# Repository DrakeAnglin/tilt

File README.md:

# Tilt

Most smart blinds need one device per blind. Tilt uses **one controller for up to three blinds**, and each blind
still has its own name in Apple Home and Alexa, its own Schedule and its own tilt.

- **One blind:** 1 tilter + 1 controller + 1 Tilt Hub.
- **Up to three blinds:** more tilters on the same controller.
- **More blinds:** another controller for each three. Still one Tilt Hub for the whole home.

Tilt is open-source, 3D-printable motorized **tilt** for cordless horizontal blinds. Each blind gets a printed tilter
in its headrail; the wand still works by hand. A battery-powered controller drives up to 3 blinds. Control is from the
**Tilt** iPhone app, **Apple Home** and **Alexa**, through a **Tilt Hub**: the controllers talk Thread to the hub and
sleep, and the hub is the Matter device for every blind. No cloud, no account.

Only the current version of each thing is kept here. Older versions are in the Git history.

## Start here
- **Build one:** [docs/build-guide.md](docs/build-guide.md): one blind start to finish, then more blinds.
- **What to buy:** [hardware/BOM.md](hardware/BOM.md), with how many of each for your number of blinds.
- **How it works:** [docs/architecture.md](docs/architecture.md). Words used everywhere: [CONTEXT.md](CONTEXT.md).
- **What to do next:** [GitHub issues](https://github.com/DrakeAnglin/tilt/issues). There are no to-do files.

## Build one
| Page | What |
|---|---|
| [build-guide.md](docs/build-guide.md) | The whole build, in order |
| [hardware/BOM.md](hardware/BOM.md) | Parts to buy, and how many |
| [measure-your-blinds.md](docs/measure-your-blinds.md) | Measuring blinds that differ from the reference blinds |
| [Tilter](hardware/mechanical/stl/tilter/README.md), [sensor module](docs/tilter-wiring.md), [mechanical build](docs/tilter-assembly.md) | Printing, wiring and assembling a tilter |
| [pcb-build.md](docs/pcb-build.md), [controller-box.md](docs/controller-box.md) | Soldering the controller PCB; the box |
| [hub-box.md](docs/hub-box.md) | The Tilt Hub's box |
| [firmware/README.md](firmware/README.md), [Tilt Hub](firmware/tilt_hub/README.md) | Flashing and updates |

## Work on Tilt
For people working on Tilt itself. You do not need any of this to build one.

| Page | What |
|---|---|
| [architecture.md](docs/architecture.md), [requirements.md](docs/requirements.md) | How it works; what it must do |
| [CONTEXT.md](CONTEXT.md) | The words used everywhere |
| [docs/adr](docs/adr) | Decisions on record |
| [docs/developer](docs/developer/README.md) | App Store notes, firmware releases, security hardening, the agent workflow |
| [pcb-v3-concept.md](docs/pcb-v3-concept.md) | The next PCB (design proposal) |

### What is in here
| Folder | What |
|---|---|
| [app/Tilt](app/README.md) | The iPhone app (SwiftUI) with its widget and Control Center buttons |
| [firmware/blinds_matter](firmware/README.md) | Controller firmware (ESP32-C6, ESP-IDF + esp-matter) |
| [firmware/tilt_hub](firmware/tilt_hub/README.md) | Tilt Hub firmware |
| [firmware/as5600_setup](firmware/README.md#as5600_setup-sensor-bench-tool) | Bench tool that switches a new AS5600 angle sensor to PWM output |
| [hardware/mechanical](hardware/mechanical/README.md) | Tilter and controller box: Fusion 360 generators and print files; headrail measurements |
| [hardware/pcb](hardware/pcb/README.md) | Controller PCB v2.2 |
| [tools](tools) | Build, check and print helpers (below) |
| [docs](docs) | Guides, notes, reference photos (`docs/reference/`) |

### Tools
| Tool | Does |
|---|---|
| `tools/fusion_tilter.py` | Builds the tilter in Fusion, runs the collision and gear checks, exports STLs |
| `tools/fusion_thin.py` | Thin-wall scan of the built tilter |
| `tools/orient.py`, `tools/bambu.py` | Turn the STLs to print orientation; build the Bambu Studio projects (PLA plate + PETG plate) |
| `tools/fusion_controller.py` | Builds the controller box in Fusion |
| `tools/flash.sh` | Builds the controller firmware and installs it through the Tilt Hub |
| `tools/flash_hub.sh` | Builds the Tilt Hub firmware and installs it over Wi-Fi; `--usb <port>` for its first flash |
| `tools/device_identity.py` | A first USB flash (`flash_hub.sh --usb`, `flash.sh --usb`): a hub's Apple Home code and setup code, made on the Mac, saved in `~/.tilt/devices/`, and its setup label (`labels` prints one again) |
| `tools/release_firmware.py` | Builds and signs a public firmware release (a version tag runs it in GitHub Actions: `docs/developer/firmware-release.md`) |
| `tools/blinds_client.py` | Talks to a controller over its secured channel (testing) |
| `tools/pcb_guide.py` | Generates the PCB build guide and its pictures |
| `tools/check_docs.py` | Checks the docs: links, anchors, and no leftovers from one house |
| `tools/firmware_tests.sh`, `tools/app_tests.sh`, `tools/test_tools.py` | Tests |
| `tools/host_cjson.py` | Finds the real cJSON (ESP-IDF's copy, else the system's) for the Tilt Hub's Mac tests |
| `tools/coverage.sh`, `tools/coverage_gate.py` | Line coverage of the tests, and the gate every pull request must pass (below) |

Fusion scripts run through the FusionBridge add-in: `python3 hardware/mechanical/fusion/fusion.py exec tools/<script>.py`.

### Coverage
<!-- coverage:start -->

| Area | Line coverage |
|---|---|
| Tilt app | at least 23% |
| controller firmware | at least 76% |
| Tilt Hub firmware | at least 17% |
| tools | at least 99% |

Every pull request covers at least 90% of the lines it changes in our own code, and no area may drop under its floor (`tools/coverage-floors.txt`). The live numbers: the `coverage` job of the [latest CI run on main](https://github.com/DrakeAnglin/tilt/actions/workflows/ci.yml?query=branch%3Amain). The rule: [docs/agents/workflow.md](docs/agents/workflow.md#coverage).
<!-- coverage:end -->

## License
- Code (firmware, app, tools, docs): [MIT](LICENSE).
- Hardware (`hardware/`: CAD, printed parts, PCB, BOM): [CC BY-NC-SA 4.0](hardware/LICENSE.md). Build it and share it, but do not sell it.

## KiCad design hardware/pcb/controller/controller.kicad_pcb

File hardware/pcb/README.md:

# Controller PCB (v2.2, carrier board)

**v2.2 (2026-11-07): the jack edge is 3.5 mm shorter.** For the controller box's end wall, the RJ12 jacks come through
the wall, so the board's jack edge moves 3.5 mm in and the jacks overhang it by 2.95 mm. Everything else is v2.1:
same parts, same copper, same holes. Only the outline moved, the ground fill pulled back with it, and the 11 ground
stitching vias that sat 2 mm from the old edge are gone. Back silkscreen reads "v2.2". The v2.1 boards already
made get the same edge cut by hand, 3–4 mm (see [the build guide, step 0](../../docs/pcb-build.md)). v2.1 as ordered
is tagged `pcb-v2.1-ordered` in git.

The controller's board: a 2-layer PCB where the **ESP32-C6 SuperMini** plugs into female header sockets; the
**18650**, the **charger** (an **Adafruit 6092**, through a 6-pin harness) and the optional **solar panel** plug into
three *different* JST headers; the **three RJ12 jacks** sit on the board edge with a fuse and
protection resistors behind each. Everything is through-hole and hand-soldered; there is no hand wiring.

The board was drawn for an MCP73871 charger module and a separate USB-C board (J3). The build now uses the Adafruit
6092 with its own USB-C instead, with no copper change: the harness and the battery splice in the J5 plug are in
[the build guide, step 11](../../docs/pcb-build.md#step-11-the-charger-the-battery-and-solar). J3 stays empty.

**Build it:** [docs/pcb-build.md](../../docs/pcb-build.md) (a picture per step). **Parts:** [BOM](../BOM.md#one-controller). **Box:** [docs/controller-box.md](../../docs/controller-box.md).

| | |
|---|---|
| Size | 47 × 121.5 mm (v2.2; v2.1 was 125), T-shaped: a 47 mm strip at the port end carries the jacks and their fuses / resistors, the 27 mm body runs alongside the 18650 |
| Layers | 2, GND poured on both and stitched with ~80 vias; 1 mm motor-return GND track from the jacks to the battery / charger GND |
| Tracks | 0.3 mm signals, 0.6–0.8 mm power; 0.2 mm clearance; vias 0.7 / 0.35 mm |
| Checks | KiCad 10: **DRC 0 violations, 0 unconnected; ERC 0 violations; schematic ↔ board parity 0 differences** (re-run 2026-11-07, v2.2) |
| Files | [schematic (PDF)](controller/controller-schematic.pdf), [controller.kicad_pro](controller/controller.kicad_pro) (open in KiCad), [parts list (CSV)](controller/controller-bom.csv) (the RJ12 jacks and fuses are only for the ports you use: buy from the [BOM](../BOM.md#parts-on-the-pcb)), [controller-pcbway.zip](controller/controller-pcbway.zip) (Gerbers + drill: upload this) |

Generated, not drawn: [netlist.py](netlist.py) holds the parts and connections; [schematic.py](schematic.py) writes the
schematic from it; [board.py](board.py) places the parts, routes the copper with [router.py](router.py), pours and
stitches GND and adds the silkscreen. Rebuild:

```bash
python3 hardware/pcb/schematic.py
/Applications/KiCad/KiCad.app/Contents/Frameworks/Python.framework/Versions/3.9/bin/python3 hardware/pcb/board.py
```

## What changed from v1 (after the peer review)
| Review item | v2 |
|---|---|
| Battery plug fits the wrong 2-pin header (could short the cell) | Three different connectors: battery JST-XH 2, charger JST-XH **6**, solar JST-**ZH** 2. The charger header is pinned **GND, BATT+, –, LOAD+, –, PWR+** so the battery's 2-pin plug, pushed into it at any offset, either lands correctly or touches one live pin: never a short |
| EN floating at boot | 100 kΩ pull-down on each EN |
| Cable lines straight into ESP pins | 220 Ω series on IN1 / IN2; **10 Ω** on EN (EN also powers the tilter's AS5600, ~6.5 mA: 220 Ω would starve it) |
| No per-port overcurrent protection | 0.75 A resettable fuse (Bel Fuse 0ZRE0075FF) on each port's battery + |
| No bulk capacitance near the jacks | 470 µF on battery + |
| Angle shifts while a motor runs | Firmware note ([firmware/README.md](../../firmware/README.md)): final reading with the motor stopped |
| Zener heat in sun | 3 W zener (1N5920B, 6.2 V) on a 5 W-size footprint (the 1N5341B's 8.9 mm body is too long for the 10.16 mm pitch, and the small panel never needs 5 W) |
| Input-power divider unfiltered | 100 nF added |
| GND pour in islands | ~80 stitching vias; filter-cap GND pads solid to the pour |
| Motor return through the analog ground | Dedicated 1 mm GND track: jacks → bulk cap → battery / charger GND |
| No test points | Pads for BAT+, 5V, 3V3, PWR, GND |
| ESP USB unreachable | ESP turned: its USB faces end B over low parts, so a cable fits with the ESP plugged in |
| No schematic | Real KiCad schematic, ERC clean, parity-checked against the board |
| Brown-out ~15 % early (Schottky to the ESP's 5V) | **Kept.** The real fix is an ideal-diode IC or a P-MOSFET with a gate driver, which are surface-mount; planned for the integrated v3 |

## Pre-order review (2026-11-02)
Checked on the files being ordered: ERC 0, DRC 0 (0 unconnected), schematic ↔ board parity 0; every ESP socket pin
traced to its GPIO; diode bands (pad 1 = cathode) and the 470 µF's + checked against their nets; drill file: 2 layers,
1.6 mm, smallest hole 0.35 mm (vias), hole counts match the parts (18 RJ12 pins, 6 jack posts, 3 mounting holes).
Added for v2.1: **+/− and pin labels on the battery, charger and solar connectors** (silkscreen only).

Things that can still be adjusted at assembly, so they don't need a new order:
- **Battery header orientation:** the 2-pin JST-XH footprint is symmetric, so the header can be soldered either way
  round. **Before soldering J4, push the cell's plug into the loose header and hold it over the footprint: the red
  wire must sit over the hole marked "+".** If not, turn the header around before soldering. (J4: pin 1 −, pin 2 +.)
- **D3 (ESP supply diode):** if the ESP browns out at low battery and you never plug USB into the ESP itself with the
  battery fitted, solder a wire link in D3's place (no 0.3 V drop).
- **Pin plan:** all in firmware (per-board pin table), no copper change.

Known limits (by design, not blockers): no reverse-battery protection beyond the keyed, labeled connectors (a
MOSFET-based one is surface-mount or a TO-220; planned for v3); each port's battery + passes a 0.75 A PTC (~0.3 Ω)
and the cord (~0.6 Ω per wire for 3 m of flat cord), which costs some motor voltage on long runs.

## Ordering
1. pcbway.com → PCB Instant Quote → **Quick-order PCB** → upload [controller-pcbway.zip](controller/controller-pcbway.zip).
2. **2 layers, FR-4, 1.6 mm, 1 oz copper, HASL lead-free**, min track / spacing **6/6 mil**, min hole **0.3 mm**,
   solder mask green (or white to match the build), silkscreen white, **quantity 5**.
3. Check the quote before paying (roughly $5–20 for 5 plus shipping). Bring one board up fully before building three.

## Pin plan (v2)
| Port | IN1 | IN2 | EN | Angle (ADC) |
|---|---|---|---|---|
| 1 | GPIO14 | GPIO18 | GPIO7 | GPIO6 |
| 2 | GPIO19 | GPIO20 | GPIO5 | GPIO4 |
| 3 | GPIO16 (TX) | GPIO17 (RX) | GPIO1 | GPIO2 |

Battery voltage GPIO3, input-power voltage GPIO0. RJ12 pinout (both ends): 1 battery +, 2 IN1, 3 GND, 4 angle, 5 EN, 6 IN2.

## Rebuild the files
```bash
K=/Applications/KiCad/KiCad.app/Contents/MacOS/kicad-cli
$K sch erc hardware/pcb/controller/controller.kicad_sch
$K pcb drc --schematic-parity hardware/pcb/controller/controller.kicad_pcb
$K pcb export gerbers --layers F.Cu,B.Cu,F.Mask,B.Mask,F.Silkscreen,B.Silkscreen,Edge.Cuts --subtract-soldermask -o hardware/pcb/controller/gerbers/ hardware/pcb/controller/controller.kicad_pcb
$K pcb export drill --format excellon --excellon-separate-th -o hardware/pcb/controller/gerbers/ hardware/pcb/controller/controller.kicad_pcb
```

## Later (v3)
Design proposal: [docs/pcb-v3-concept.md](../../docs/pcb-v3-concept.md). Nothing is ordered yet.

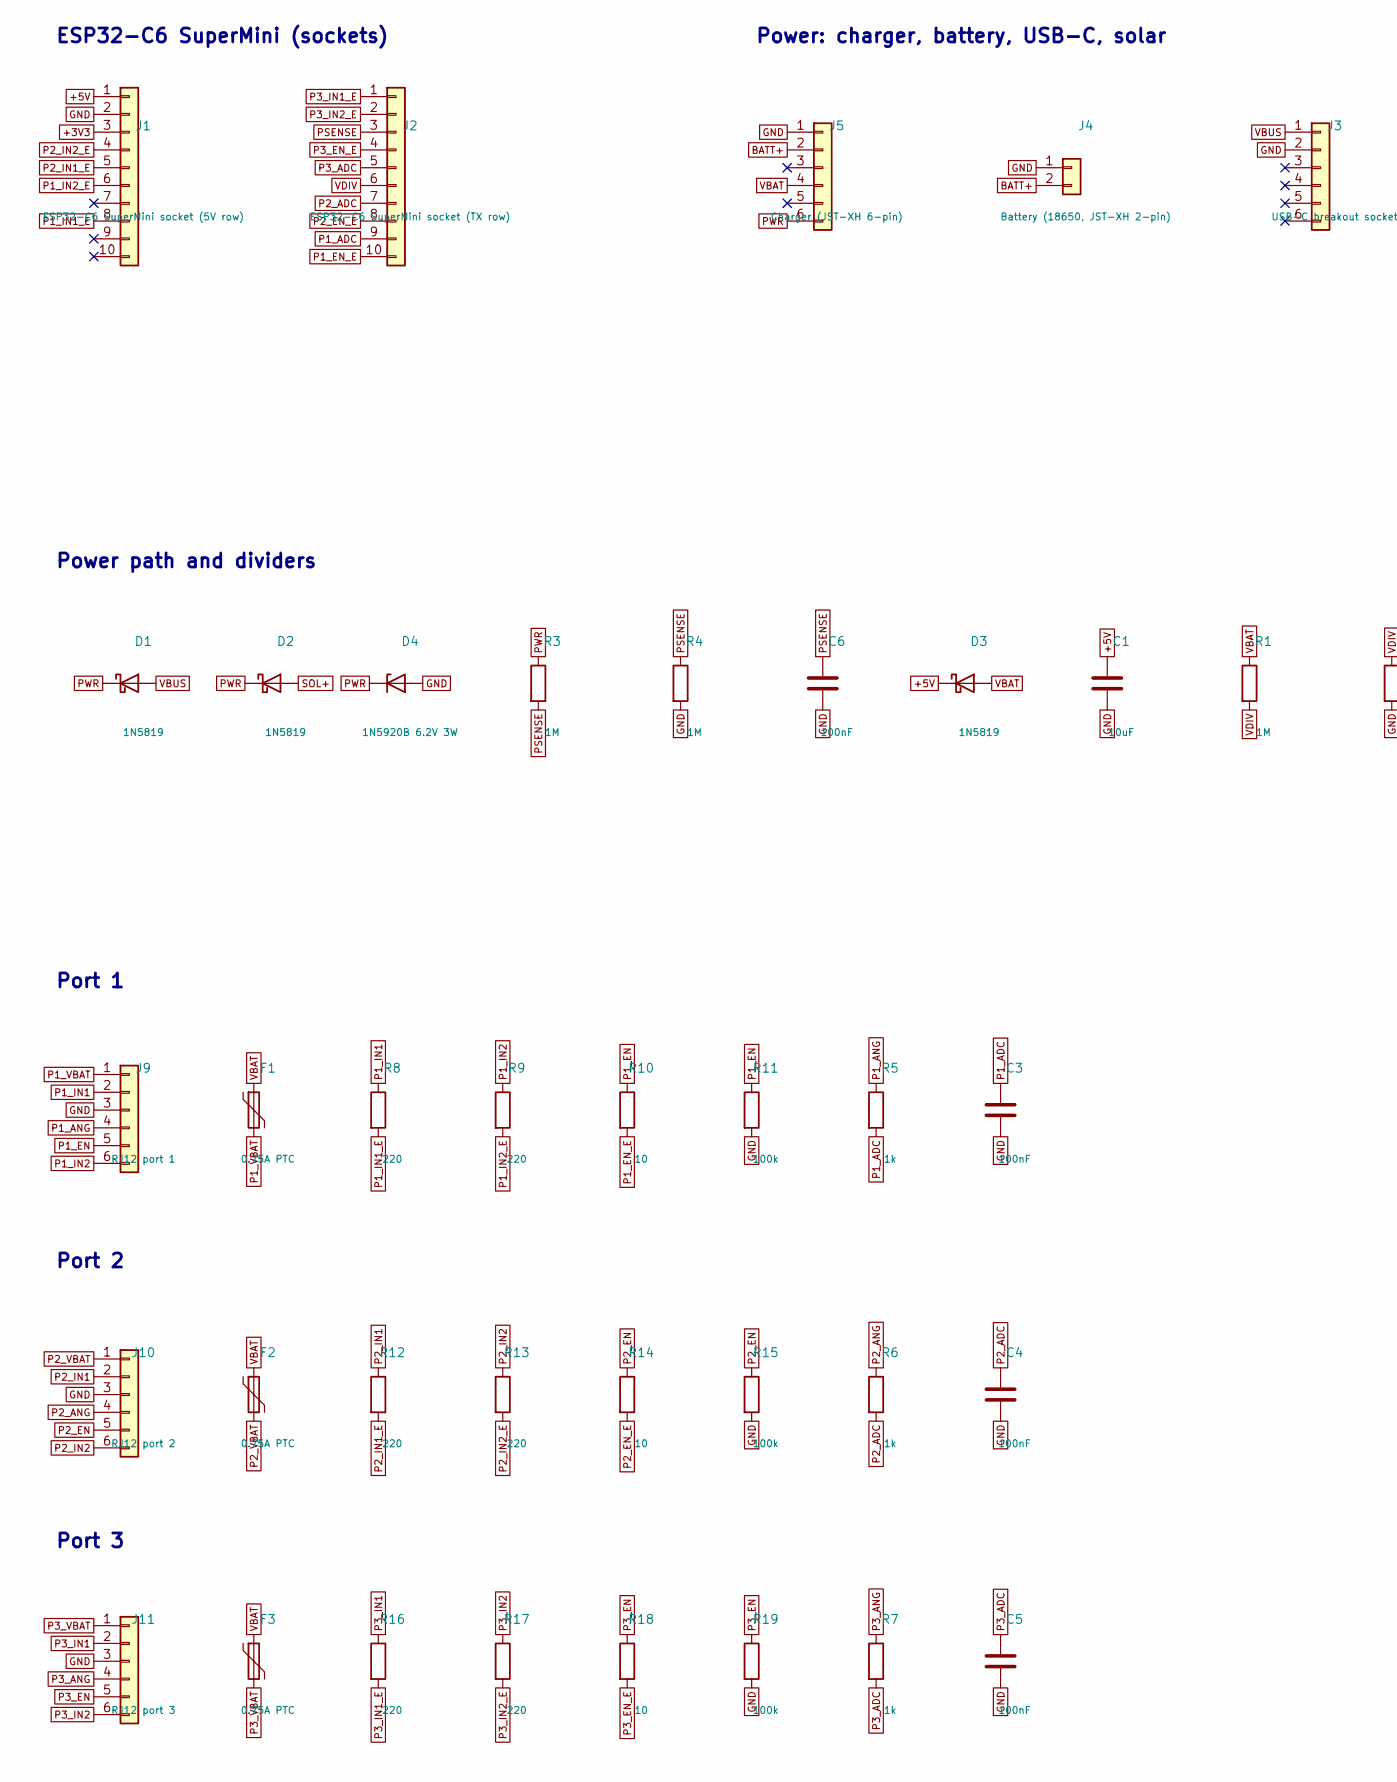
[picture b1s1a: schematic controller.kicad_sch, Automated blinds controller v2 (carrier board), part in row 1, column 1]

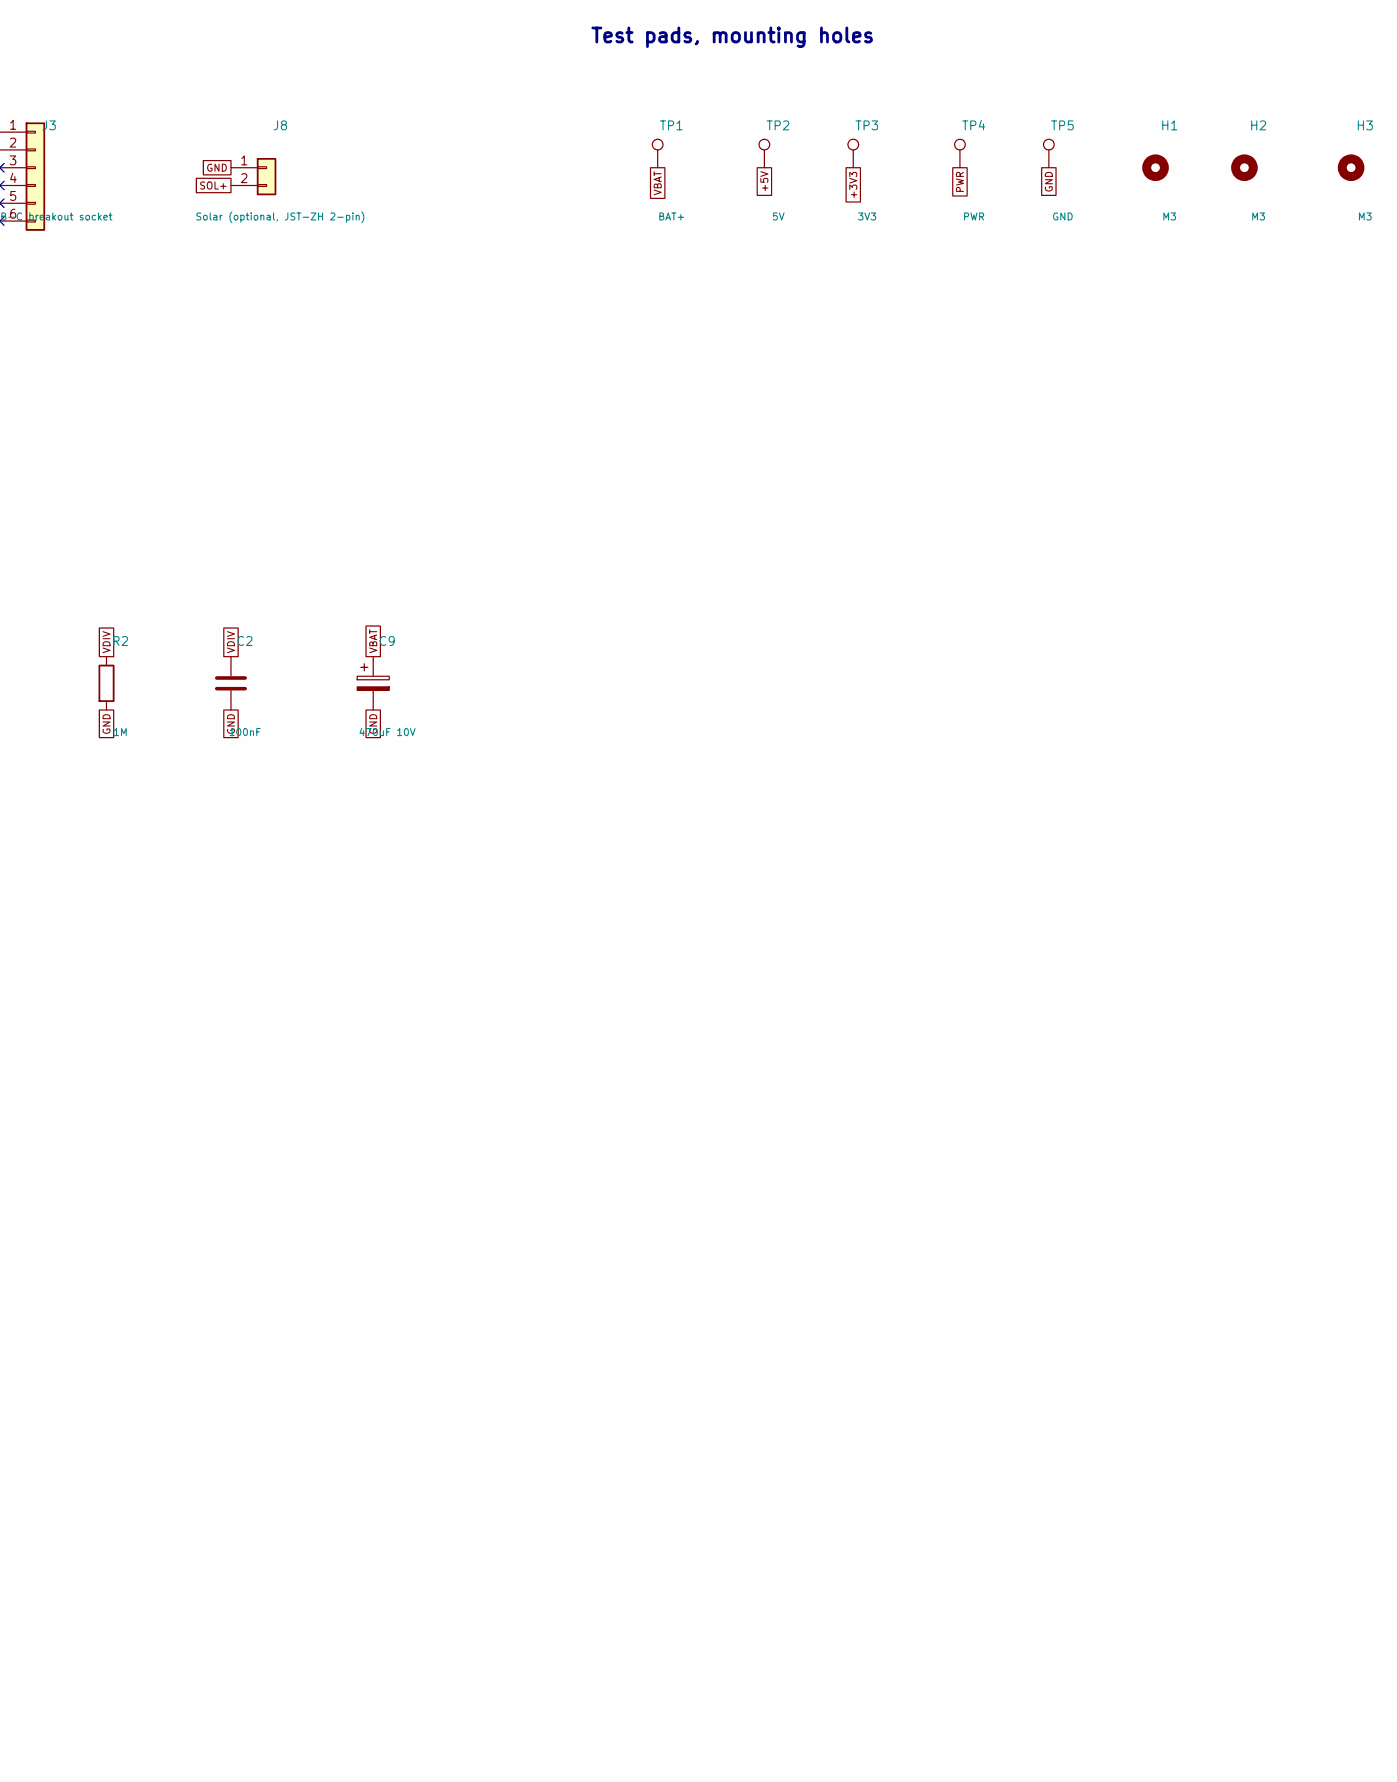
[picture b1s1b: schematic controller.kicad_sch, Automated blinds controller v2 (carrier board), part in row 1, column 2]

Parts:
C1: 10uF; C_Disc_D5.0mm_W2.5mm_P5.00mm
C2, C3, C4, C5, C6: 100nF; C_Disc_D5.0mm_W2.5mm_P5.00mm
C9: 470uF 10V; CP_Radial_D8.0mm_P3.50mm
D1, D2, D3: 1N5819; D_DO-41_SOD81_P7.62mm_Horizontal
D4: 1N5920B 6.2V 3W; D_5W_P10.16mm_Horizontal
F1, F2, F3: 0.75A PTC; Fuse_BelFuse_0ZRE0075FF_L11.5mm_W4.8mm
H1, H2, H3: M3; MountingHole_3.2mm_M3
J1: ESP32-C6 SuperMini socket (5V row); PinSocket_1x10_P2.54mm_Vertical
J2: ESP32-C6 SuperMini socket (TX row); PinSocket_1x10_P2.54mm_Vertical
J3: USB-C breakout socket; PinSocket_1x06_P2.54mm_Vertical
J4: Battery (18650, JST-XH 2-pin); JST_XH_B2B-XH-A_1x02_P2.50mm_Vertical
J5: Charger (JST-XH 6-pin); JST_XH_B6B-XH-A_1x06_P2.50mm_Vertical
J8: Solar (optional, JST-ZH 2-pin); JST_ZH_B2B-ZR_1x02_P1.50mm_Vertical
J9: RJ12 port 1; RJ12_Amphenol_54601-x06_Horizontal
J10: RJ12 port 2; RJ12_Amphenol_54601-x06_Horizontal
J11: RJ12 port 3; RJ12_Amphenol_54601-x06_Horizontal
R1, R2, R3, R4: 1M; R_Axial_DIN0207_L6.3mm_D2.5mm_P7.62mm_Horizontal
R5, R6, R7: 1k; R_Axial_DIN0207_L6.3mm_D2.5mm_P7.62mm_Horizontal
R8, R9, R12, R13, R16, R17: 220; R_Axial_DIN0207_L6.3mm_D2.5mm_P7.62mm_Horizontal
R10, R14, R18: 10; R_Axial_DIN0207_L6.3mm_D2.5mm_P7.62mm_Horizontal
R11, R15, R19: 100k; R_Axial_DIN0207_L6.3mm_D2.5mm_P7.62mm_Horizontal
TP1: BAT+; TestPoint_THTPad_1.5x1.5mm_Drill0.7mm
TP2: 5V; TestPoint_THTPad_1.5x1.5mm_Drill0.7mm
TP3: 3V3; TestPoint_THTPad_1.5x1.5mm_Drill0.7mm
TP4: PWR; TestPoint_THTPad_1.5x1.5mm_Drill0.7mm
TP5: GND; TestPoint_THTPad_1.5x1.5mm_Drill0.7mm

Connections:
+3V3: J1.3, TP3.1
+5V: C1.1, D3.1 (K), J1.1, TP2.1
BATT+: J4.2, J5.2
GND: C1.2, C2.2, C3.2, C4.2, C5.2, C6.2, C9.2, D4.2 (A), J1.2, J3.2, J4.1, J5.1, J8.1, J9.3, J10.3, J11.3, R2.2, R4.2, R11.2, R15.2, R19.2, TP5.1
P1_ADC: C3.1, J2.9, R5.2
P1_ANG: J9.4, R5.1
P1_EN: J9.5, R10.1, R11.1
P1_EN_E: J2.10, R10.2
P1_IN1: J9.2, R8.1
P1_IN1_E: J1.8, R8.2
P1_IN2: J9.6, R9.1
P1_IN2_E: J1.6, R9.2
P1_VBAT: F1.2, J9.1
P2_ADC: C4.1, J2.7, R6.2
P2_ANG: J10.4, R6.1
P2_EN: J10.5, R14.1, R15.1
P2_EN_E: J2.8, R14.2
P2_IN1: J10.2, R12.1
P2_IN1_E: J1.5, R12.2
P2_IN2: J10.6, R13.1
P2_IN2_E: J1.4, R13.2
P2_VBAT: F2.2, J10.1
P3_ADC: C5.1, J2.5, R7.2
P3_ANG: J11.4, R7.1
P3_EN: J11.5, R18.1, R19.1
P3_EN_E: J2.4, R18.2
P3_IN1: J11.2, R16.1
P3_IN1_E: J2.1, R16.2
P3_IN2: J11.6, R17.1
P3_IN2_E: J2.2, R17.2
P3_VBAT: F3.2, J11.1
PSENSE: C6.1, J2.3, R3.2, R4.1
PWR: D1.1 (K), D2.1 (K), D4.1 (K), J5.6, R3.1, TP4.1
SOL+: D2.2 (A), J8.2
VBAT: C9.1, D3.2 (A), F1.1, F2.1, F3.1, J5.4, R1.1, TP1.1
VBUS: D1.2 (A), J3.1
VDIV: C2.1, J2.6, R1.2, R2.1

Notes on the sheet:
ESP32-C6 SuperMini (sockets)
Power: charger, battery, USB-C, solar
Power path and dividers
Port 1
Port 2
Port 3
Test pads, mounting holes

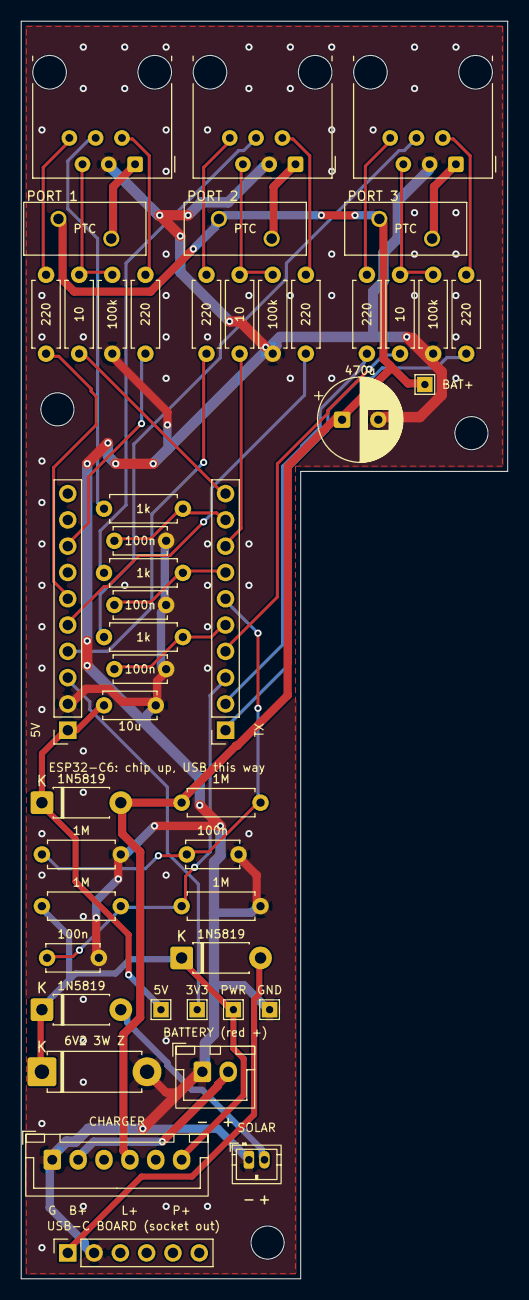
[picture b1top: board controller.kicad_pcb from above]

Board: 2 copper layers, 47.0 x 121.5 mm, 50 parts (0 on the bottom side), 37 nets.

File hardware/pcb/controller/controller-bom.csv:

"Reference","Value","Footprint","QUANTITY"
"C1","10uF","Capacitor_THT:C_Disc_D5.0mm_W2.5mm_P5.00mm","1"
"C2-C6","100nF","Capacitor_THT:C_Disc_D5.0mm_W2.5mm_P5.00mm","5"
"C9","470uF 10V","Capacitor_THT:CP_Radial_D8.0mm_P3.50mm","1"
"D1-D3","1N5819","Diode_THT:D_DO-41_SOD81_P7.62mm_Horizontal","3"
"D4","1N5920B 6.2V 3W","Diode_THT:D_5W_P10.16mm_Horizontal","1"
"F1-F3","0.75A PTC","Fuse:Fuse_BelFuse_0ZRE0075FF_L11.5mm_W4.8mm","3"
"J1","ESP32-C6 SuperMini socket (5V row)","Connector_PinSocket_2.54mm:PinSocket_1x10_P2.54mm_Vertical","1"
"J2","ESP32-C6 SuperMini socket (TX row)","Connector_PinSocket_2.54mm:PinSocket_1x10_P2.54mm_Vertical","1"
"J3","USB-C breakout socket","Connector_PinSocket_2.54mm:PinSocket_1x06_P2.54mm_Vertical","1"
"J4","Battery (18650, JST-XH 2-pin)","Connector_JST:JST_XH_B2B-XH-A_1x02_P2.50mm_Vertical","1"
"J5","Charger (JST-XH 6-pin)","Connector_JST:JST_XH_B6B-XH-A_1x06_P2.50mm_Vertical","1"
"J8","Solar (optional, JST-ZH 2-pin)","Connector_JST:JST_ZH_B2B-ZR_1x02_P1.50mm_Vertical","1"
"J9","RJ12 port 1","Connector_RJ:RJ12_Amphenol_54601-x06_Horizontal","1"
"J10","RJ12 port 2","Connector_RJ:RJ12_Amphenol_54601-x06_Horizontal","1"
"J11","RJ12 port 3","Connector_RJ:RJ12_Amphenol_54601-x06_Horizontal","1"
"R1-R4","1M","Resistor_THT:R_Axial_DIN0207_L6.3mm_D2.5mm_P7.62mm_Horizontal","4"
"R5-R7","1k","Resistor_THT:R_Axial_DIN0207_L6.3mm_D2.5mm_P7.62mm_Horizontal","3"
"R8,R9,R12,R13,R16,R17","220","Resistor_THT:R_Axial_DIN0207_L6.3mm_D2.5mm_P7.62mm_Horizontal","6"
"R10,R14,R18","10","Resistor_THT:R_Axial_DIN0207_L6.3mm_D2.5mm_P7.62mm_Horizontal","3"
"R11,R15,R19","100k","Resistor_THT:R_Axial_DIN0207_L6.3mm_D2.5mm_P7.62mm_Horizontal","3"
